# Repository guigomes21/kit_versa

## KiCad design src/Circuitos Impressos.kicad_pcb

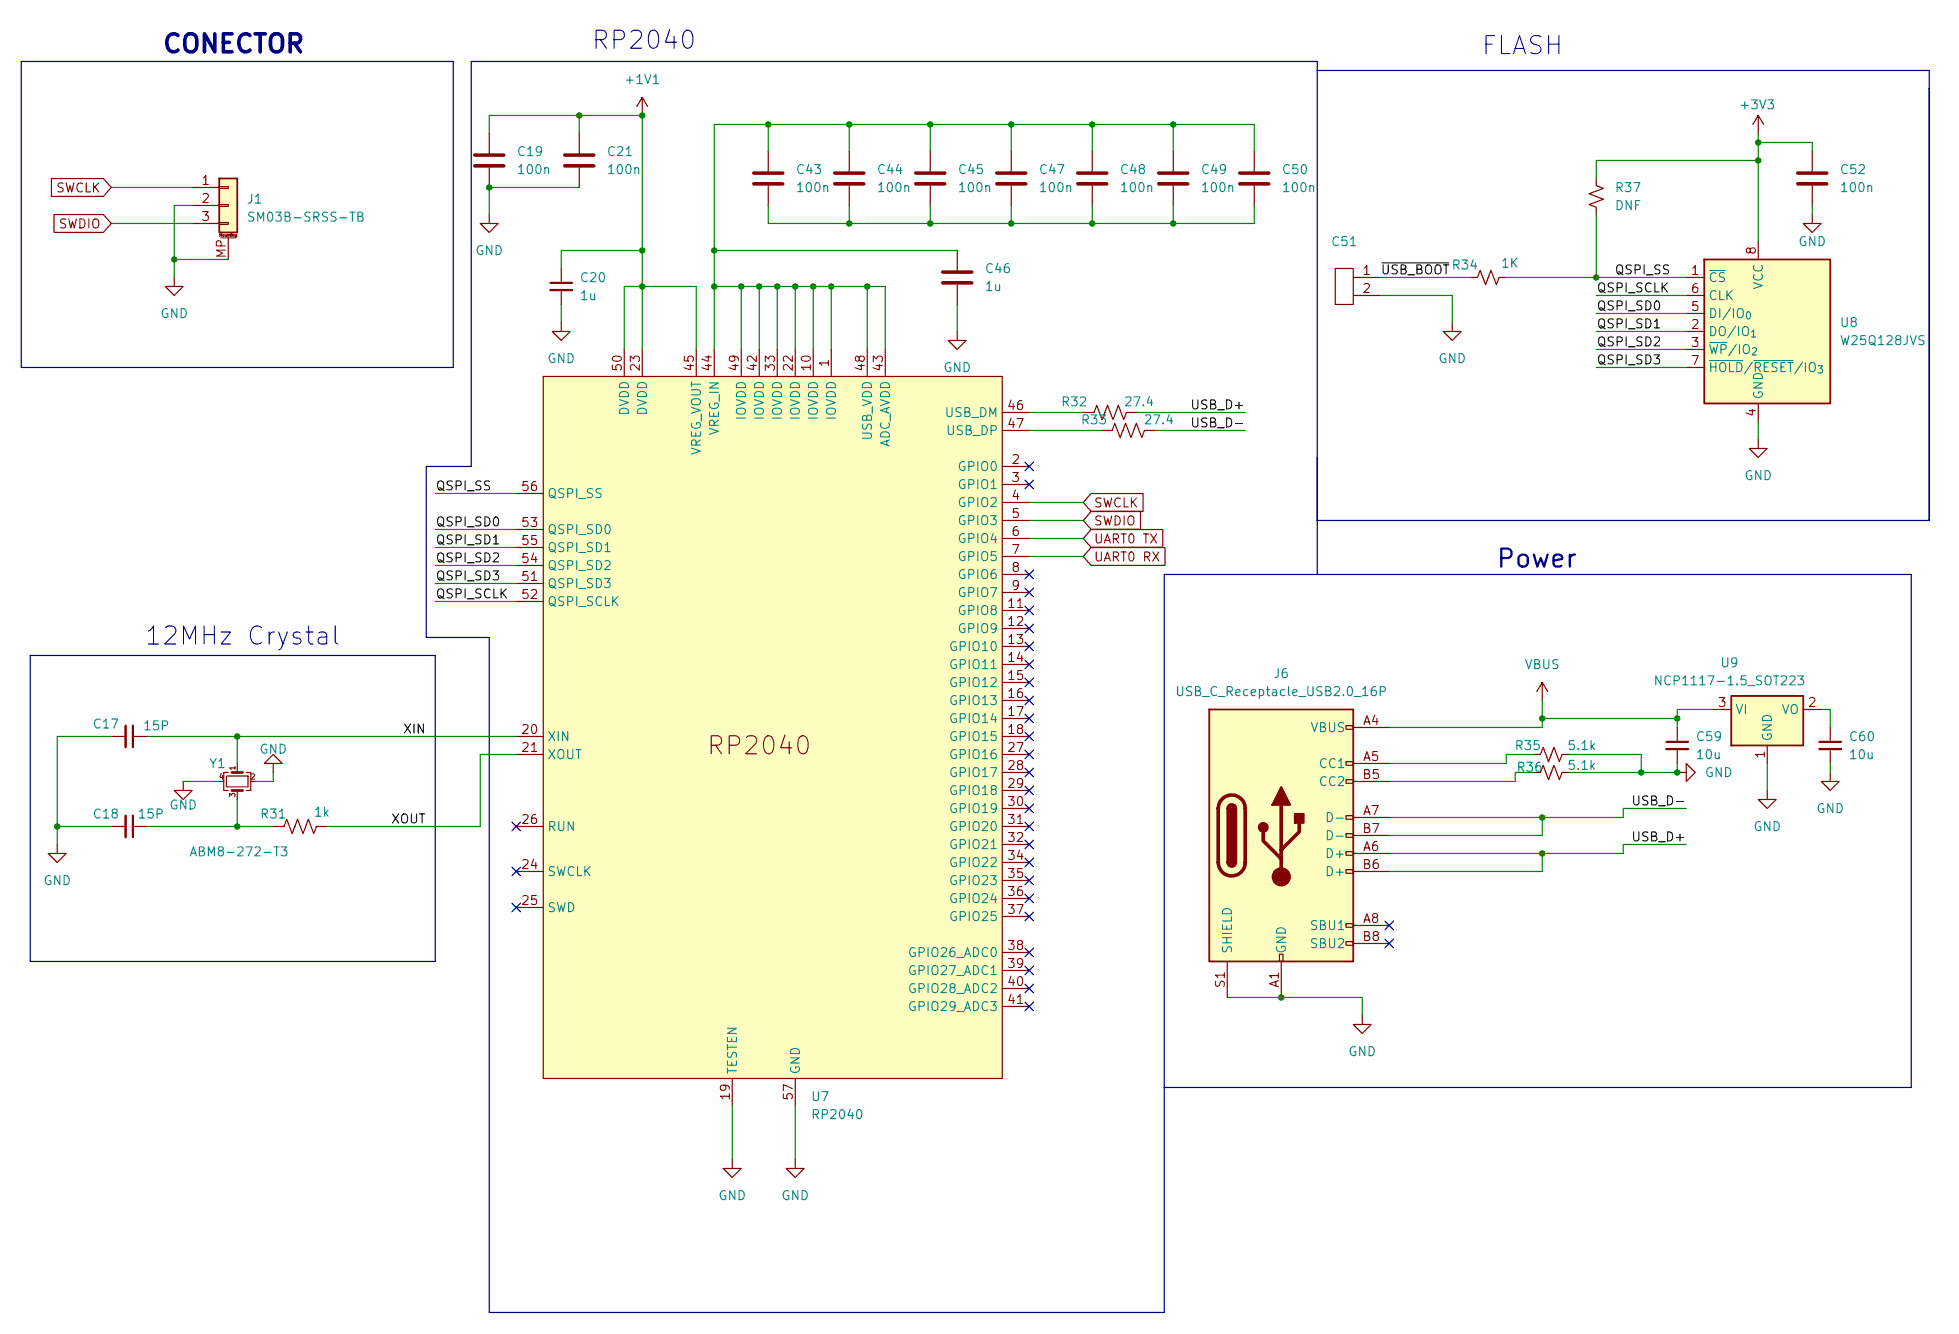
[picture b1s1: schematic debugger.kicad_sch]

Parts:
C17, C18: 15P; C_0402_1005Metric
C19, C21, C43, C44, C45, C47, C48, C49, C50, C52: 100n; C_0402_1005Metric
C20, C46: 1u; C_0402_1005Metric
C51: PinHeader_1x02_P1.00mm_Horizontal
C59, C60: 10u; C_0402_1005Metric
J1: SM03B-SRSS-TB; JST_SH_SM03B-SRSS-TB_1x03-1MP_P1.00mm_Horizontal
J6: USB_C_Receptacle_USB2.0_16P; USB_C_Receptacle_GCT_USB4105-xx-A_16P_TopMnt_Horizontal
R31: 1k; R_0402_1005Metric
R32, R33: 27.4; R_0402_1005Metric
R34: 1K; R_0402_1005Metric
R35, R36: 5.1k; R_0402_1005Metric
R37: DNF; R_0402_1005Metric
U7: RP2040
U8: W25Q128JVS; SOIC-8_5.3x5.3mm_P1.27mm
U9: NCP1117-1.5_SOT223; SOT-223-3_TabPin2
Y1: ABM8-272-T3; Crystal_SMD_Abracon_ABM8AIG-4Pin_3.2x2.5mm

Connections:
/debugger_RP2040/QSPI_SCLK: U7.52 (QSPI_SCLK), U8.6 (CLK)
/debugger_RP2040/QSPI_SD0: U7.53 (QSPI_SD0), U8.5 (DI/IO_{0})
/debugger_RP2040/QSPI_SD1: U7.55 (QSPI_SD1), U8.2 (DO/IO_{1})
/debugger_RP2040/QSPI_SD2: U7.54 (QSPI_SD2), U8.3 (~WP/IO_{2})
/debugger_RP2040/QSPI_SD3: U7.51 (QSPI_SD3), U8.7 (~HOLD/~RESET/IO_{3})
/debugger_RP2040/QSPI_SS: R34.2, R37.2, U7.56 (QSPI_SS), U8.1 (~CS)
/debugger_RP2040/USB_D+: J6.A6 (D+), J6.B6 (D+), R32.2
/debugger_RP2040/USB_D-: J6.A7 (D-), J6.B7 (D-), R33.2
/debugger_RP2040/XIN: C17.1, U7.20 (XIN), Y1.1
/debugger_RP2040/XOUT: R31.2, U7.21 (XOUT)
/debugger_RP2040/~USB_BOOT: C51.1, R34.1
unnamed: C18.1, R31.1, Y1.3
unnamed: C43.2, C44.2, C45.2, C47.2, C48.2, C49.2, C50.2
unnamed: J6.A5 (CC1), R35.2
unnamed: J6.B5 (CC2), R36.2
unnamed: R32.1, U7.46 (USB_DM)
unnamed: R33.1, U7.47 (USB_DP)
unnamed: C60.1, U9.2 (VO)
SWCLK: J1.1, U7.4 (GPIO2); also elsewhere on the board
SWDIO: J1.3, U7.5 (GPIO3); also elsewhere on the board
UART0 RX: U7.7 (GPIO5); also elsewhere on the board
UART0 TX: U7.6 (GPIO4); also elsewhere on the board
VBUS: C59.1, J6.A4 (VBUS), J6.A9 (VBUS), J6.B4 (VBUS), J6.B9 (VBUS), U9.3 (VI); also elsewhere on the board

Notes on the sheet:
Power
FLASH
12MHz Crystal
CONECTOR
RP2040

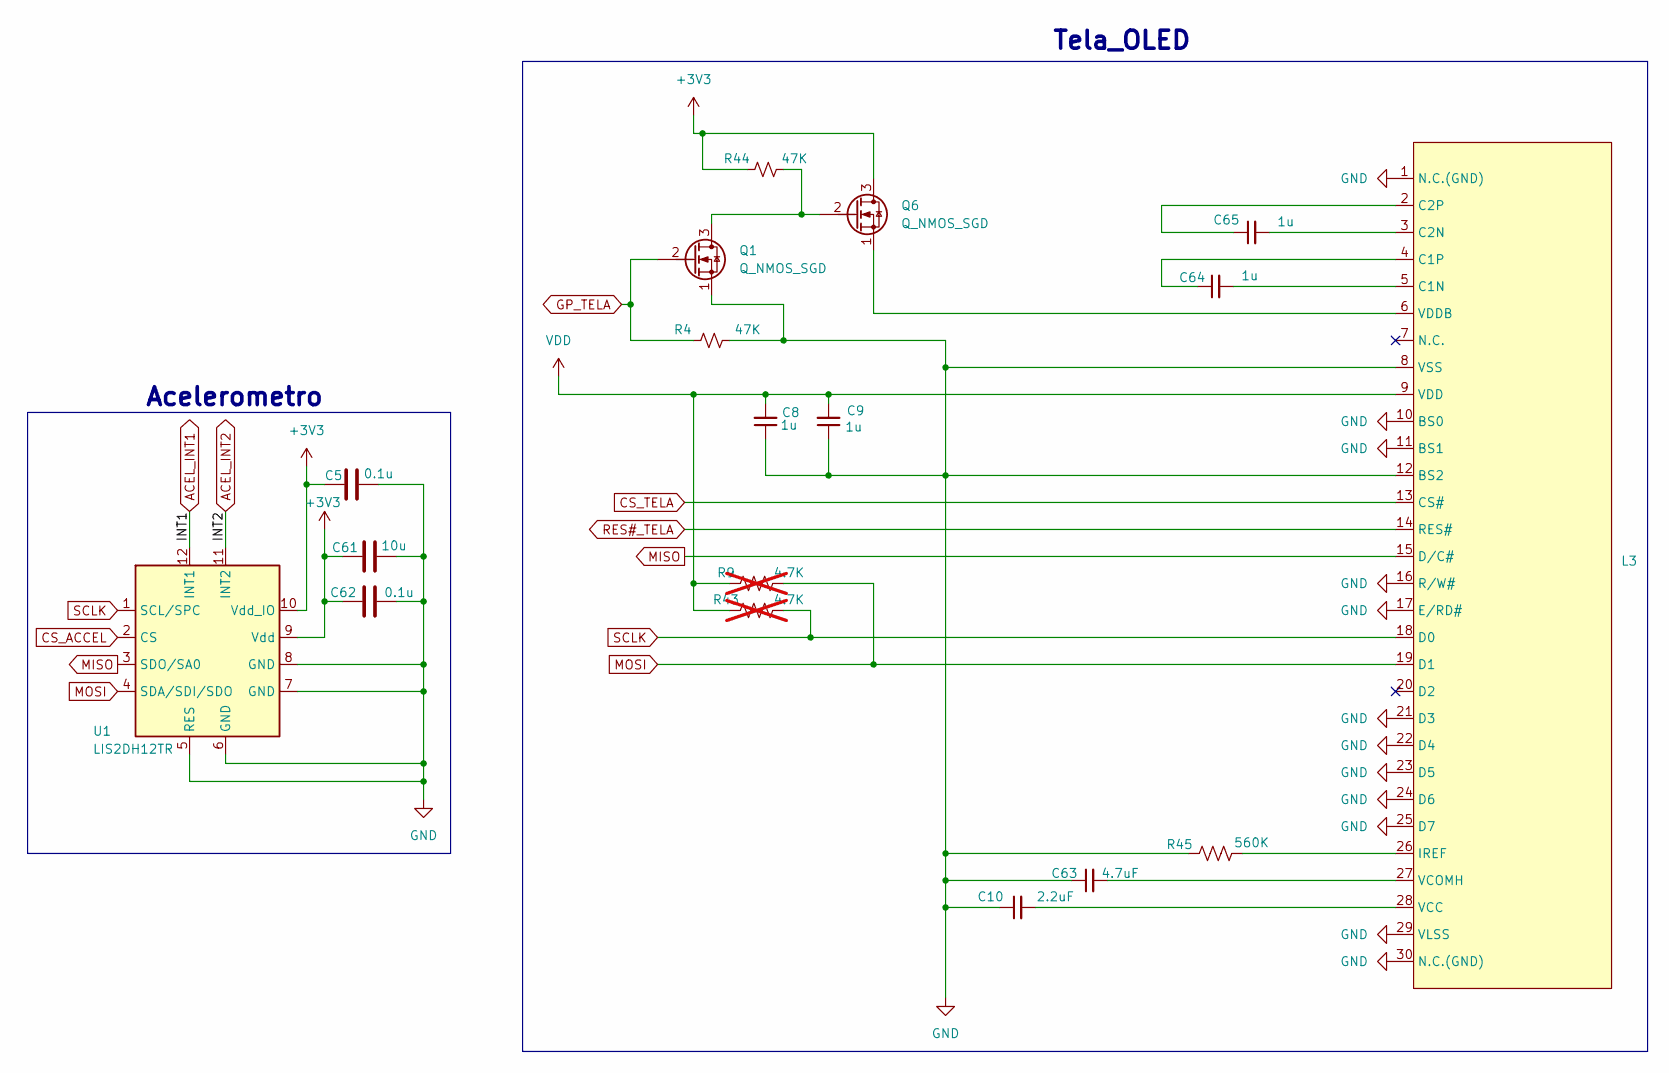
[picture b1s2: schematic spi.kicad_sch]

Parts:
C5, C62: 0.1u; C_0402_1005Metric
C8, C9, C64, C65: 1u; C_0402_1005Metric
C10: 2.2uF; C_0402_1005Metric
C61: 10u; C_0402_1005Metric
C63: 4.7uF; C_0402_1005Metric
L3: OLED-128O064D
Q1, Q6: Q_NMOS_SGD; mosfet-DMN2600UFB-7
R4, R44: 47K; R_0402_1005Metric
R9, R43: 4.7K; R_0402_1005Metric; not fitted
R45: 560K; R_0402_1005Metric
U1: LIS2DH12TR; LGA-14_2x2mm_P0.35mm_LayoutBorder3x4y

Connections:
CS_ACCEL: U1.2 (CS); also elsewhere on the board
CS_TELA: L3.13 (CS#); also elsewhere on the board
GP_TELA: Q1.2 (G), R4.1; also elsewhere on the board
MISO: L3.15 (D/C#), U1.3 (SDO/SA0); also elsewhere on the board
MOSI: L3.19 (D1), R9.2, U1.4 (SDA/SDI/SDO); also elsewhere on the board
unnamed: C64.2, L3.5 (C1N)
unnamed: C64.1, L3.4 (C1P)
unnamed: C65.2, L3.3 (C2N)
unnamed: C65.1, L3.2 (C2P)
unnamed: L3.26 (IREF), R45.2
unnamed: C10.2, L3.28 (VCC)
unnamed: C63.2, L3.27 (VCOMH)
unnamed: L3.6 (VDDB), Q6.1 (S)
unnamed: Q1.3 (D), Q6.2 (G), R44.2
RES#_TELA: L3.14 (RES#); also elsewhere on the board
SCLK: L3.18 (D0), R43.2, U1.1 (SCL/SPC); also elsewhere on the board
VDD: C8.2, C9.2, L3.9 (VDD), R9.1, R43.1

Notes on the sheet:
Tela_OLED
Acelerometro

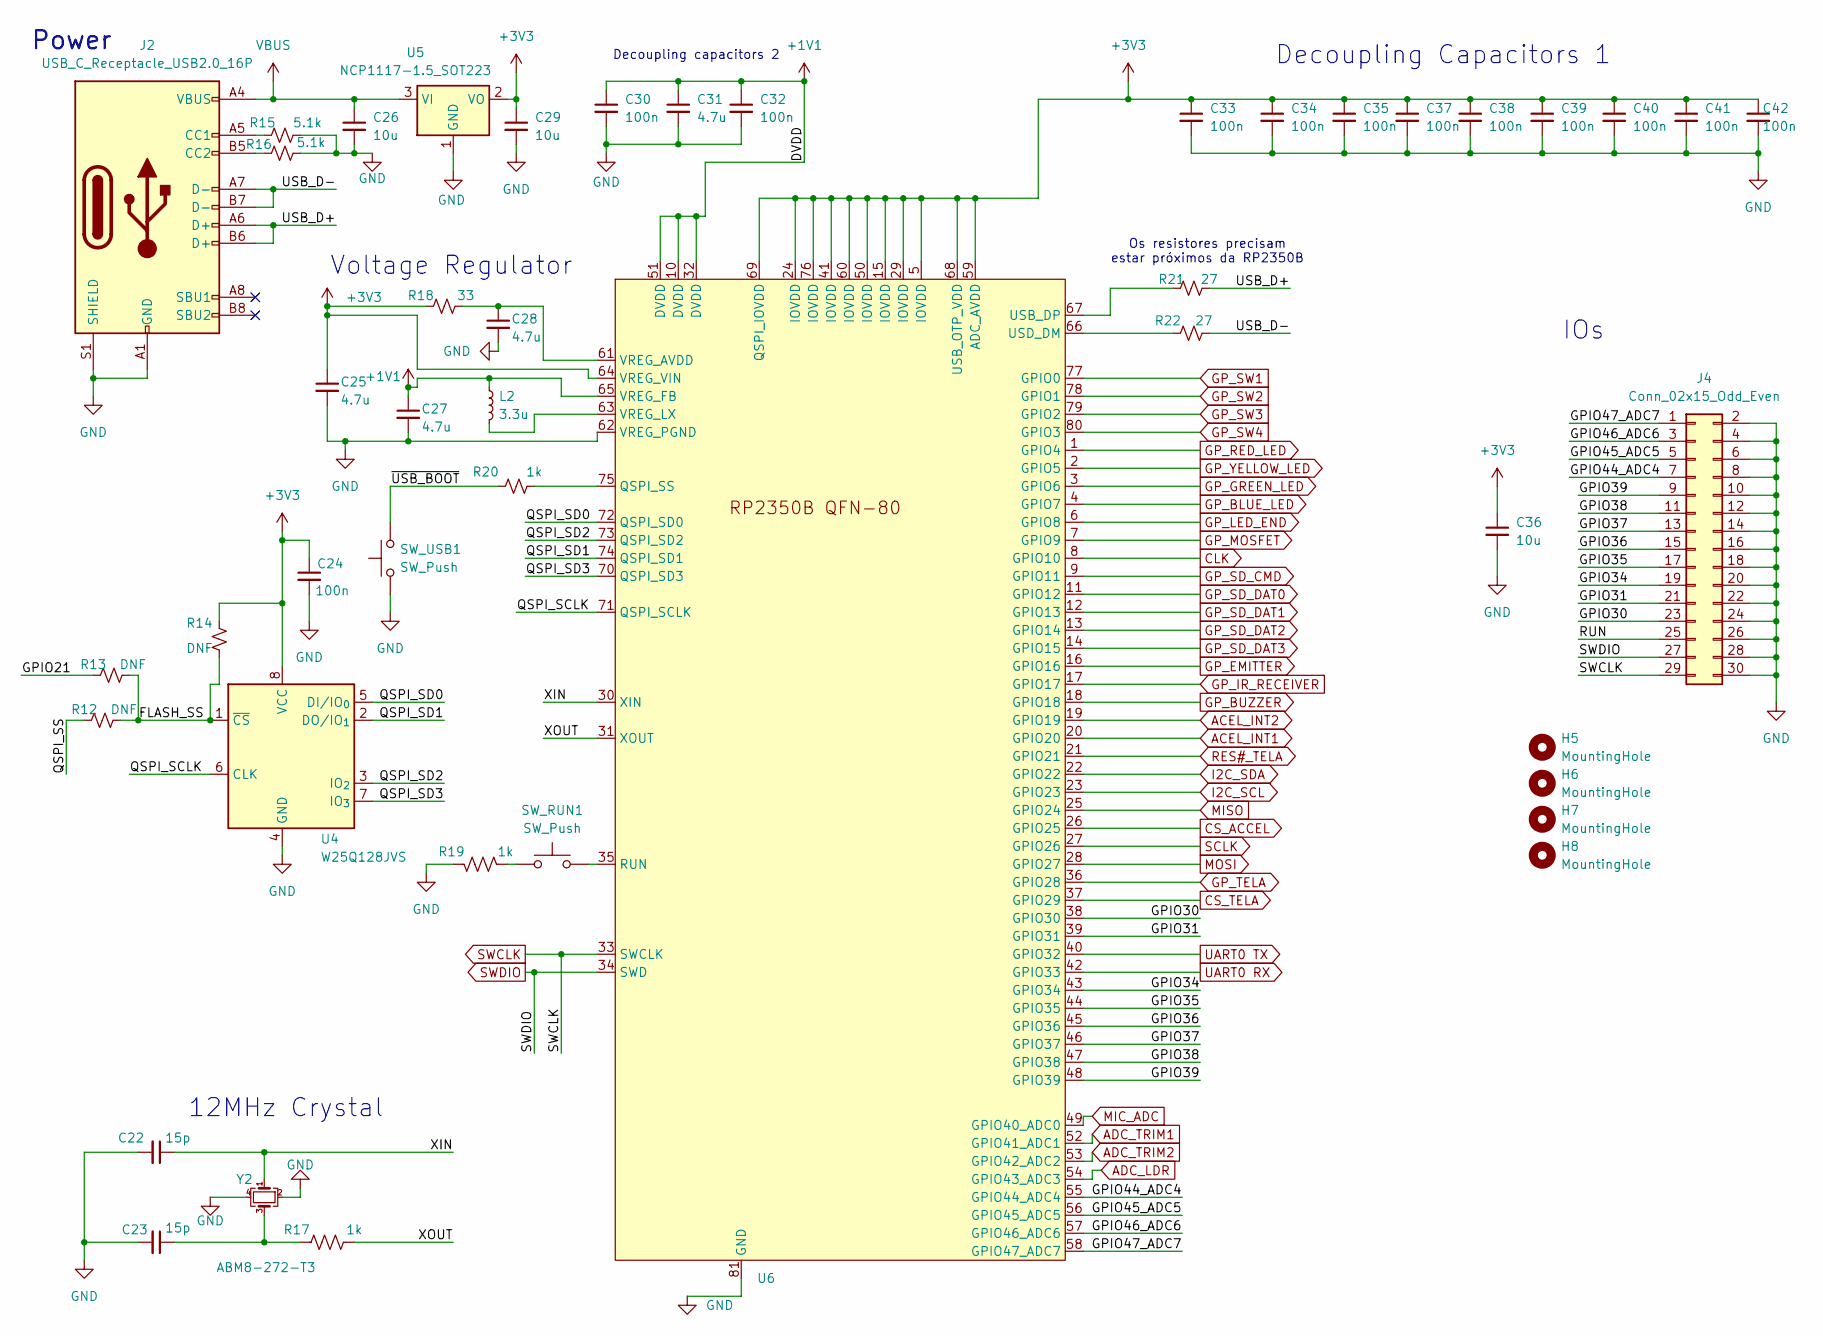
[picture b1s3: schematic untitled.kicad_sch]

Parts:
C22, C23: 15p; C_0402_1005Metric
C24: 100n; C_01005_0402Metric
C25, C27, C28, C31: 4.7u; C_0402_1005Metric
C26, C29, C36: 10u; C_0402_1005Metric
C30, C32, C33, C34, C35, C37, C38, C39, C40, C41, C42: 100n; C_0402_1005Metric
H5, H6, H7, H8: MountingHole; MountingHole_2.2mm_M2
J2: USB_C_Receptacle_USB2.0_16P; USB_C_Receptacle_GCT_USB4105-xx-A_16P_TopMnt_Horizontal
J4: Conn_02x15_Odd_Even; PinHeader_2x15_P1.00mm_Vertical_SMD
L2: 3.3u; L_0402_1005Metric
R12, R13, R14: DNF; R_0402_1005Metric
R15, R16: 5.1k; R_0402_1005Metric
R17, R19, R20: 1k; R_0402_1005Metric
R18: 33; R_0402_1005Metric
R21, R22: 27; R_0402_1005Metric
SW_RUN1: SW_Push; SW_Tactile_SPST_NO_Straight_CK_PTS636Sx25SMTRLFS
SW_USB1: SW_Push; SW_Push_1P1T_NO_CK_PTS125Sx43PSMTR
U4: W25Q128JVS; SOIC-8_5.3x5.3mm_P1.27mm
U5: NCP1117-1.5_SOT223; SOT-223-3_TabPin2
U6: RP2350B
Y2: ABM8-272-T3; Crystal_SMD_Abracon_ABM8AIG-4Pin_3.2x2.5mm

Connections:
/MCU_RP2350/FLASH_SS: R12.2, R13.2, R14.1, U4.1 (~CS)
/MCU_RP2350/GPIO21: R13.1
/MCU_RP2350/GPIO30: J4.23, U6.38 (GPIO30)
/MCU_RP2350/GPIO31: J4.21, U6.39 (GPIO31)
/MCU_RP2350/GPIO34: J4.19, U6.43 (GPIO34)
/MCU_RP2350/GPIO35: J4.17, U6.44 (GPIO35)
/MCU_RP2350/GPIO36: J4.15, U6.45 (GPIO36)
/MCU_RP2350/GPIO37: J4.13, U6.46 (GPIO37)
/MCU_RP2350/GPIO38: J4.11, U6.47 (GPIO38)
/MCU_RP2350/GPIO39: J4.9, U6.48 (GPIO39)
/MCU_RP2350/GPIO44_ADC4: J4.7, U6.55 (GPIO44_ADC4)
/MCU_RP2350/GPIO45_ADC5: J4.5, U6.56 (GPIO45_ADC5)
/MCU_RP2350/GPIO46_ADC6: J4.3, U6.57 (GPIO46_ADC6)
/MCU_RP2350/GPIO47_ADC7: J4.1, U6.58 (GPIO47_ADC7)
/MCU_RP2350/QSPI_SCLK: U4.6 (CLK), U6.71 (QSPI_SCLK)
/MCU_RP2350/QSPI_SD0: U4.5 (DI/IO_{0}), U6.72 (QSPI_SD0)
/MCU_RP2350/QSPI_SD1: U4.2 (DO/IO_{1}), U6.74 (QSPI_SD1)
/MCU_RP2350/QSPI_SD2: U4.3 (IO_{2}), U6.73 (QSPI_SD2)
/MCU_RP2350/QSPI_SD3: U4.7 (IO_{3}), U6.70 (QSPI_SD3)
/MCU_RP2350/QSPI_SS: R12.1
/MCU_RP2350/RUN: J4.25
/MCU_RP2350/USB_D+: J2.A6 (D+), J2.B6 (D+), R21.2
/MCU_RP2350/USB_D-: J2.A7 (D-), J2.B7 (D-), R22.2
/MCU_RP2350/XIN: C22.1, U6.30 (XIN), Y2.1
/MCU_RP2350/XOUT: R17.2, U6.31 (XOUT)
/MCU_RP2350/~USB_BOOT: R20.1, SW_USB1.2
ADC_LDR: U6.54 (GPIO43_ADC3); also elsewhere on the board
ADC_TRIM1: U6.52 (GPIO41_ADC1); also elsewhere on the board
ADC_TRIM2: U6.53 (GPIO42_ADC2); also elsewhere on the board
CLK: U6.8 (GPIO10); also elsewhere on the board
CS_ACCEL: U6.26 (GPIO25); also elsewhere on the board
CS_TELA: U6.37 (GPIO29); also elsewhere on the board
GP_BLUE_LED: U6.4 (GPIO7); also elsewhere on the board
GP_BUZZER: U6.18 (GPIO18); also elsewhere on the board
GP_EMITTER: U6.16 (GPIO16)
GP_GREEN_LED: U6.3 (GPIO6); also elsewhere on the board
GP_IR_RECEIVER: U6.17 (GPIO17); also elsewhere on the board
GP_LED_END: U6.6 (GPIO8); also elsewhere on the board
GP_MOSFET: U6.7 (GPIO9); also elsewhere on the board
GP_RED_LED: U6.1 (GPIO4); also elsewhere on the board
GP_SD_CMD: U6.9 (GPIO11); also elsewhere on the board
GP_SD_DAT0: U6.11 (GPIO12); also elsewhere on the board
GP_SD_DAT1: U6.12 (GPIO13); also elsewhere on the board
GP_SD_DAT2: U6.13 (GPIO14); also elsewhere on the board
GP_SD_DAT3: U6.14 (GPIO15); also elsewhere on the board
GP_SW1: U6.77 (GPIO0); also elsewhere on the board
GP_SW2: U6.78 (GPIO1)
GP_SW3: U6.79 (GPIO2); also elsewhere on the board
GP_SW4: U6.80 (GPIO3); also elsewhere on the board
GP_TELA: U6.36 (GPIO28); also elsewhere on the board
GP_YELLOW_LED: U6.2 (GPIO5); also elsewhere on the board
I2C_SCL: U6.23 (GPIO23); also elsewhere on the board
I2C_SDA: U6.22 (GPIO22); also elsewhere on the board
MIC_ADC: U6.49 (GPIO40_ADC0); also elsewhere on the board
MISO: U6.25 (GPIO24); also elsewhere on the board
MOSI: U6.28 (GPIO27); also elsewhere on the board
unnamed: C23.1, R17.1, Y2.3
unnamed: J2.A5 (CC1), R15.2
unnamed: J2.B5 (CC2), R16.2
unnamed: R19.1, SW_RUN1.1
unnamed: R20.2, U6.75 (QSPI_SS)
unnamed: SW_RUN1.2, U6.35 (RUN)
unnamed: R21.1, U6.67 (USB_DP)
unnamed: R22.1, U6.66 (USD_DM)
unnamed: C28.1, R18.1, U6.61 (VREG_AVDD)
unnamed: L2.2, U6.63 (VREG_LX)
RES#_TELA: U6.21 (GPIO21); also elsewhere on the board
SCLK: U6.27 (GPIO26); also elsewhere on the board
SWCLK: J4.29, U6.33 (SWCLK); also elsewhere on the board
SWDIO: J4.27, U6.34 (SWD); also elsewhere on the board
UART0 RX: U6.42 (GPIO33); also elsewhere on the board
UART0 TX: U6.40 (GPIO32); also elsewhere on the board
VBUS: C26.1, J2.A4 (VBUS), J2.A9 (VBUS), J2.B4 (VBUS), J2.B9 (VBUS), U5.3 (VI); also elsewhere on the board

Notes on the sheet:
12MHz Crystal
Power
Decoupling Capacitors 1
Os resistores precisam estar próximos da RP2350B
IOs
Decoupling capacitors 2
Voltage Regulator

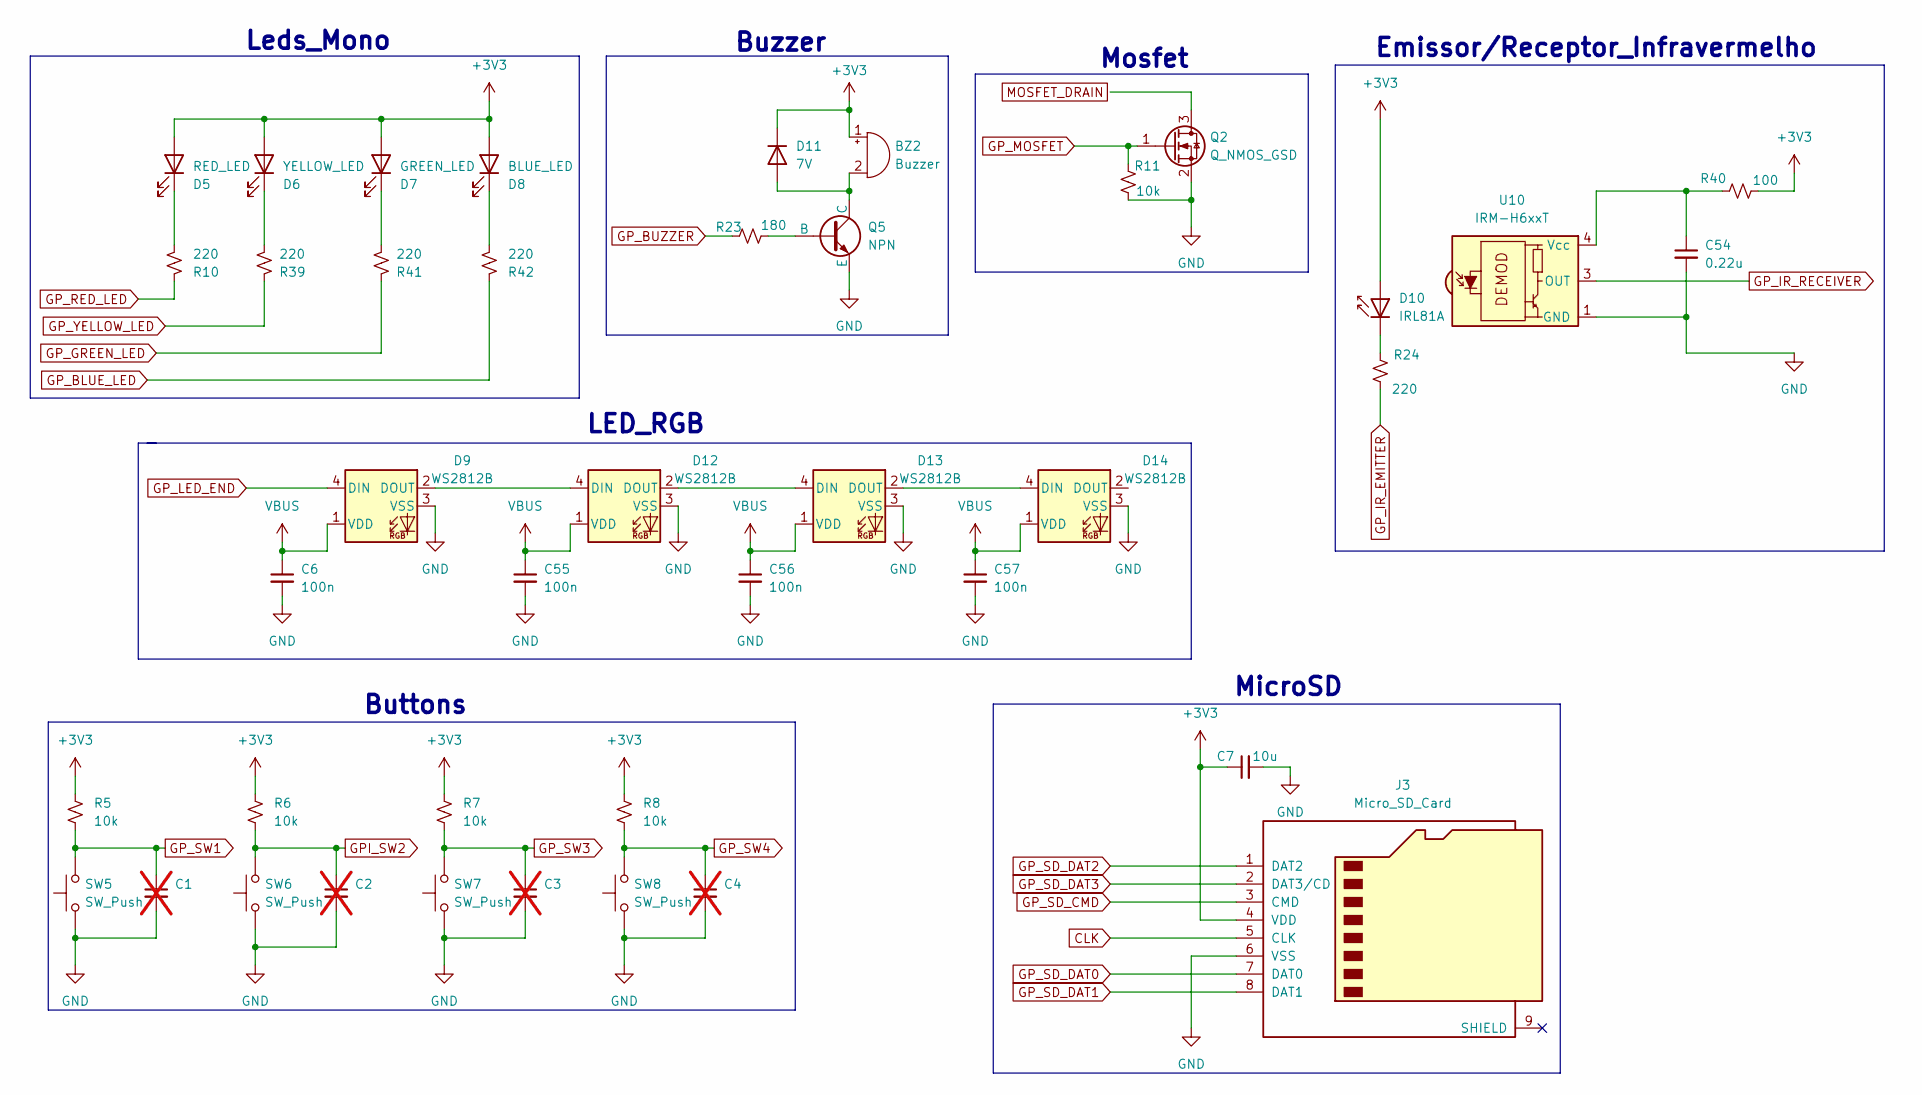
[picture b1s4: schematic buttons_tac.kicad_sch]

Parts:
BZ2: Buzzer; Buzzer_12x9.5RM7.6
C1, C2, C3, C4: C_0402_1005Metric; not fitted
C6, C55, C56, C57: 100n; C_0402_1005Metric
C7: 10u; C_0402_1005Metric
C54: 0.22u; C_0402_1005Metric
D5: RED_LED; LED_0603_1608Metric
D6: YELLOW_LED; LED_0603_1608Metric
D7: GREEN_LED; LED_0603_1608Metric
D8: BLUE_LED; LED_0603_1608Metric
D9, D12, D13, D14: WS2812B; LED_WS2812B_PLCC4_5.0x5.0mm_P3.2mm
D10: IRL81A; IR_emitter_B13V1IR--20C000114U1930
D11: 7V; D_SOD-523
J3: Micro_SD_Card; microSD_HC_Wuerth_693072010801
Q2: Q_NMOS_GSD; mosfet-DMN2600UFB-7
Q5: NPN; transistor - DTC014E SOT-416FL
R5, R6, R7, R8, R11: 10k; R_0402_1005Metric
R10, R24, R39, R41, R42: 220; R_0402_1005Metric
R23: 180; R_0402_1005Metric
R40: 100; R_0402_1005Metric
SW5, SW6, SW7, SW8: SW_Push; SW_Tactile_SPST_NO_Straight_CK_PTS636Sx25SMTRLFS
U10: IRM-H6xxT; Everlight_IRM-H6xxT

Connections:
CLK: J3.5 (CLK); also elsewhere on the board
GPI_SW2: C2.1, R6.2, SW6.2
GP_BLUE_LED: R42.1; also elsewhere on the board
GP_BUZZER: R23.2; also elsewhere on the board
GP_GREEN_LED: R41.1; also elsewhere on the board
GP_IR_EMITTER: R24.2
GP_IR_RECEIVER: U10.3 (OUT); also elsewhere on the board
GP_LED_END: D9.4 (DIN); also elsewhere on the board
GP_MOSFET: Q2.1 (G), R11.1; also elsewhere on the board
GP_RED_LED: R10.1; also elsewhere on the board
GP_SD_CMD: J3.3 (CMD); also elsewhere on the board
GP_SD_DAT0: J3.7 (DAT0); also elsewhere on the board
GP_SD_DAT1: J3.8 (DAT1); also elsewhere on the board
GP_SD_DAT2: J3.1 (DAT2); also elsewhere on the board
GP_SD_DAT3: J3.2 (DAT3/CD); also elsewhere on the board
GP_SW1: C1.1, R5.2, SW5.2; also elsewhere on the board
GP_SW3: C3.1, R7.2, SW7.2; also elsewhere on the board
GP_SW4: C4.1, R8.2, SW8.2; also elsewhere on the board
GP_YELLOW_LED: R39.1; also elsewhere on the board
unnamed: BZ2.2 (-), D11.2 (A), Q5.1 (C)
unnamed: D5.1 (K), R10.2
unnamed: D6.1 (K), R39.2
unnamed: D7.1 (K), R41.2
unnamed: D8.1 (K), R42.2
unnamed: D10.1 (K), R24.1
unnamed: D9.2 (DOUT), D12.4 (DIN)
unnamed: D12.2 (DOUT), D13.4 (DIN)
unnamed: D13.2 (DOUT), D14.4 (DIN)
unnamed: Q5.2 (B), R23.1
unnamed: C54.1, R40.1, U10.4 (Vcc)
VBUS: C6.1, C55.1, C56.1, C57.1, D9.1 (VDD), D12.1 (VDD), D13.1 (VDD), D14.1 (VDD); also elsewhere on the board

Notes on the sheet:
Mosfet
Emissor/Receptor_Infravermelho
LED_RGB
Buzzer
MicroSD
Buttons
Leds_Mono

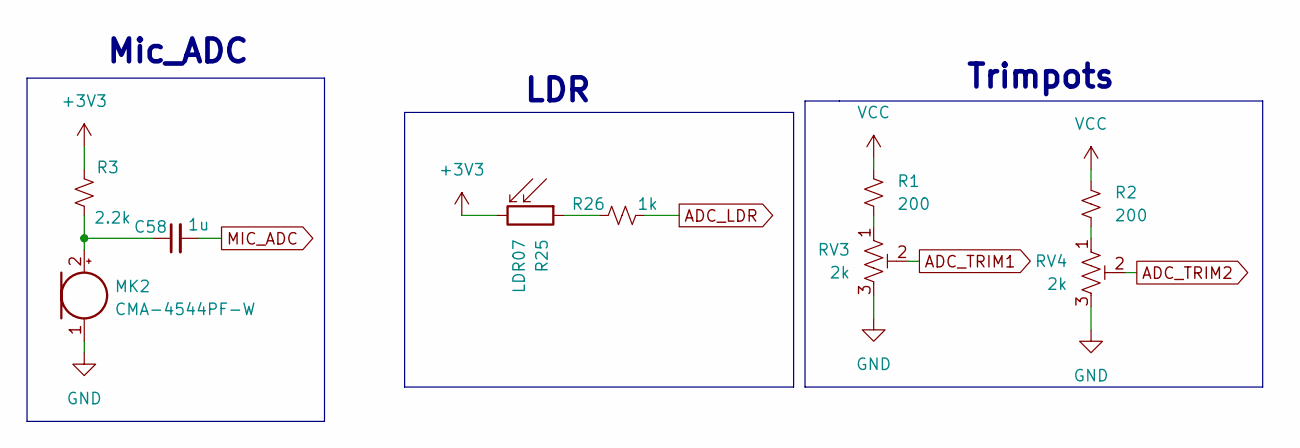
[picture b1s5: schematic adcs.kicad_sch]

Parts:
C58: 1u; C_0402_1005Metric
MK2: CMA-4544PF-W; MIC_CMA-4544PF-W
R1, R2: 200; R_0402_1005Metric
R3: 2.2k; R_0402_1005Metric
R25: LDR07; R_LDR_5.1x4.3mm_P3.4mm_Vertical
R26: 1k; R_0402_1005Metric
RV3, RV4: 2k; Potentiometer_Bourns_TC33X_Vertical

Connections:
ADC_LDR: R26.1; also elsewhere on the board
ADC_TRIM1: RV3.2; also elsewhere on the board
ADC_TRIM2: RV4.2; also elsewhere on the board
MIC_ADC: C58.2; also elsewhere on the board
unnamed: C58.1, MK2.2 (+), R3.2
unnamed: R1.2, RV3.1
unnamed: R2.2, RV4.1
unnamed: R25.1, R26.2
VCC: R1.1, R2.1

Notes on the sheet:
Mic_ADC
Trimpots
LDR

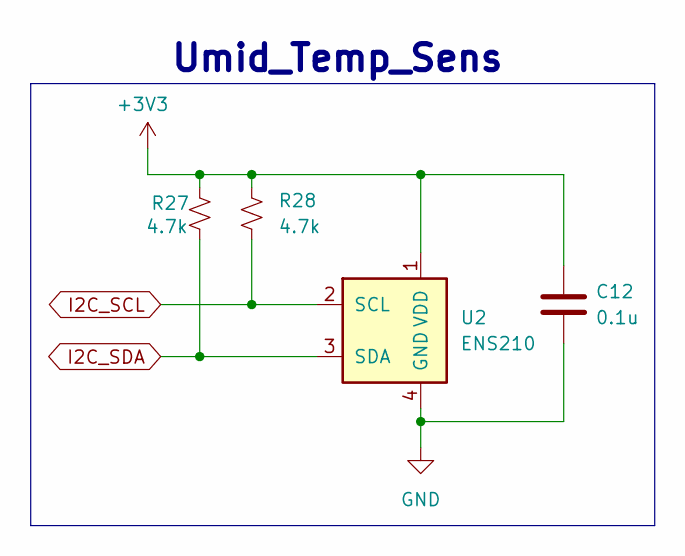
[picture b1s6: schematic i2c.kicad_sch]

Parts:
C12: 0.1u; C_0402_1005Metric
R27, R28: 4.7k; R_0402_1005Metric
U2: ENS210; AMS_QFN-4-1EP_2x2mm_P0.95mm_EP0.7x1.6mm

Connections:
I2C_SCL: R28.2, U2.2 (SCL); also elsewhere on the board
I2C_SDA: R27.2, U2.3 (SDA); also elsewhere on the board

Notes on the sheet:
Umid_Temp_Sens

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
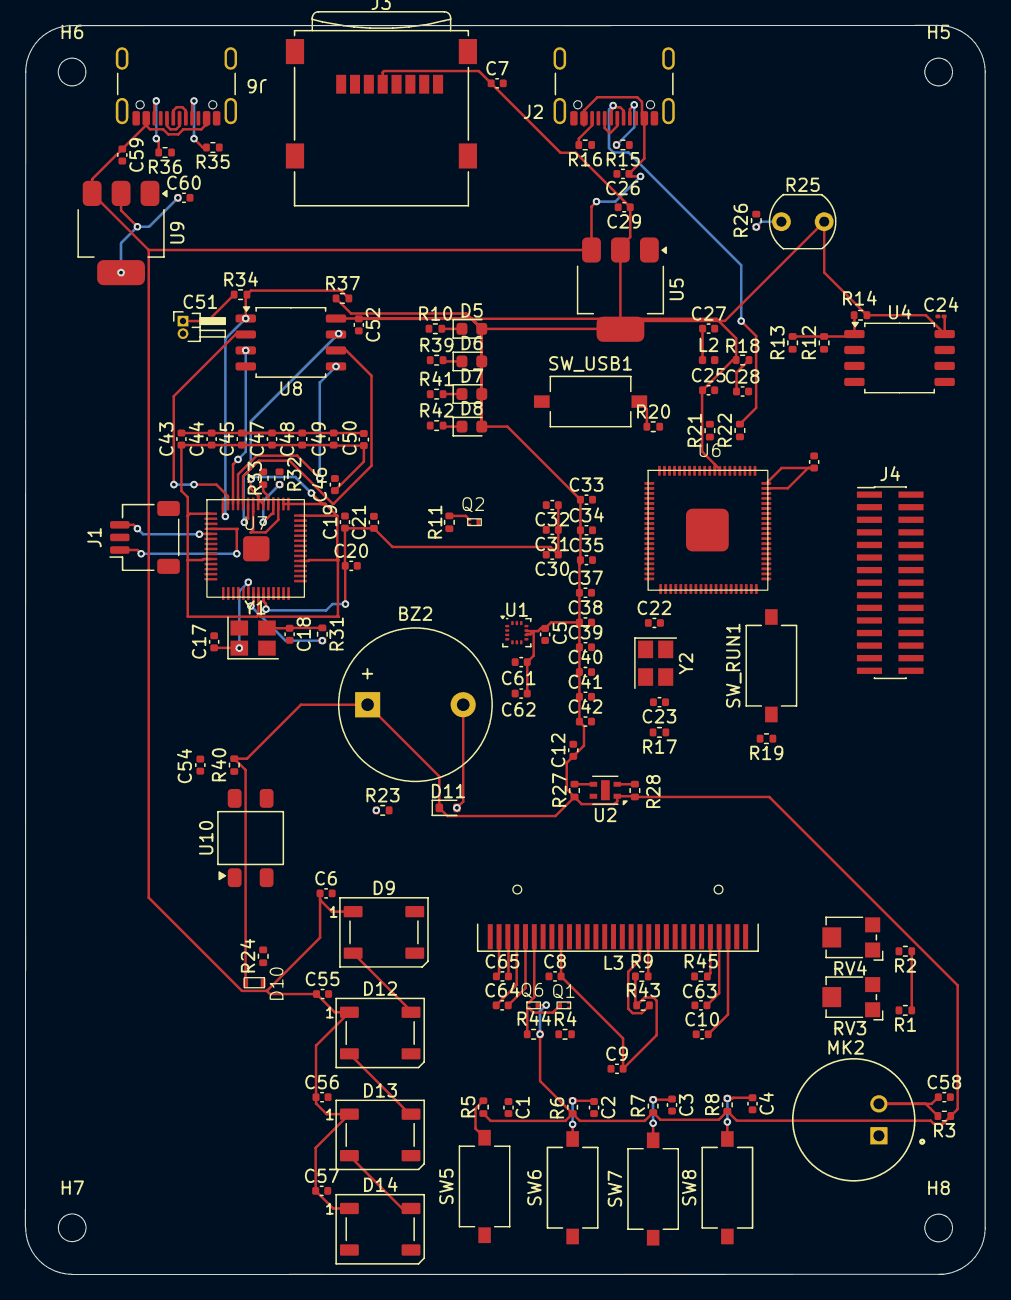
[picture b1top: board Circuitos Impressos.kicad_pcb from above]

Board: 4 copper layers, 76.3 x 99.3 mm, 146 parts (0 on the bottom side), 118 nets.

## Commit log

2025-06-27 Esquemático Adicionado
2025-06-30 fix: Consertando paginação e refact da Tela_OLED
2025-06-30 revisão da RP2040
2025-07-01 FEAT: adicionando footprints
2025-07-01 LDR adicionado
2025-07-01 footprints MCU ok
2025-07-01 Footprints adicionados GPIOS
2025-07-01 footprints adicionados componentes elétricos GPIOS
2025-07-02 adicionado footprints, falta microfone e display somente
2025-07-03 pequenos ajustes nas tags
2025-07-03 Bugs na att da PCI resolvidos (falta só a tela OLED)
2025-07-03 Subconjuntos organizados na PCI
2025-07-03 placement finalizado, faltando trilhas
2025-07-04 FEAT: Trilhas parcialmente adicionadas
